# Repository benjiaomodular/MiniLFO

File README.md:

# MiniLFO

A super simple 2HP triangle wave LFO for Eurorack modular synth. This is roughly based on [David Haillant's Simple LFO](https://www.davidhaillant.com/wp/wp-content/uploads/lfo-1.5b-20210205.pdf).

More info on my website: https://benjiaomodular.com/posts/minilfo

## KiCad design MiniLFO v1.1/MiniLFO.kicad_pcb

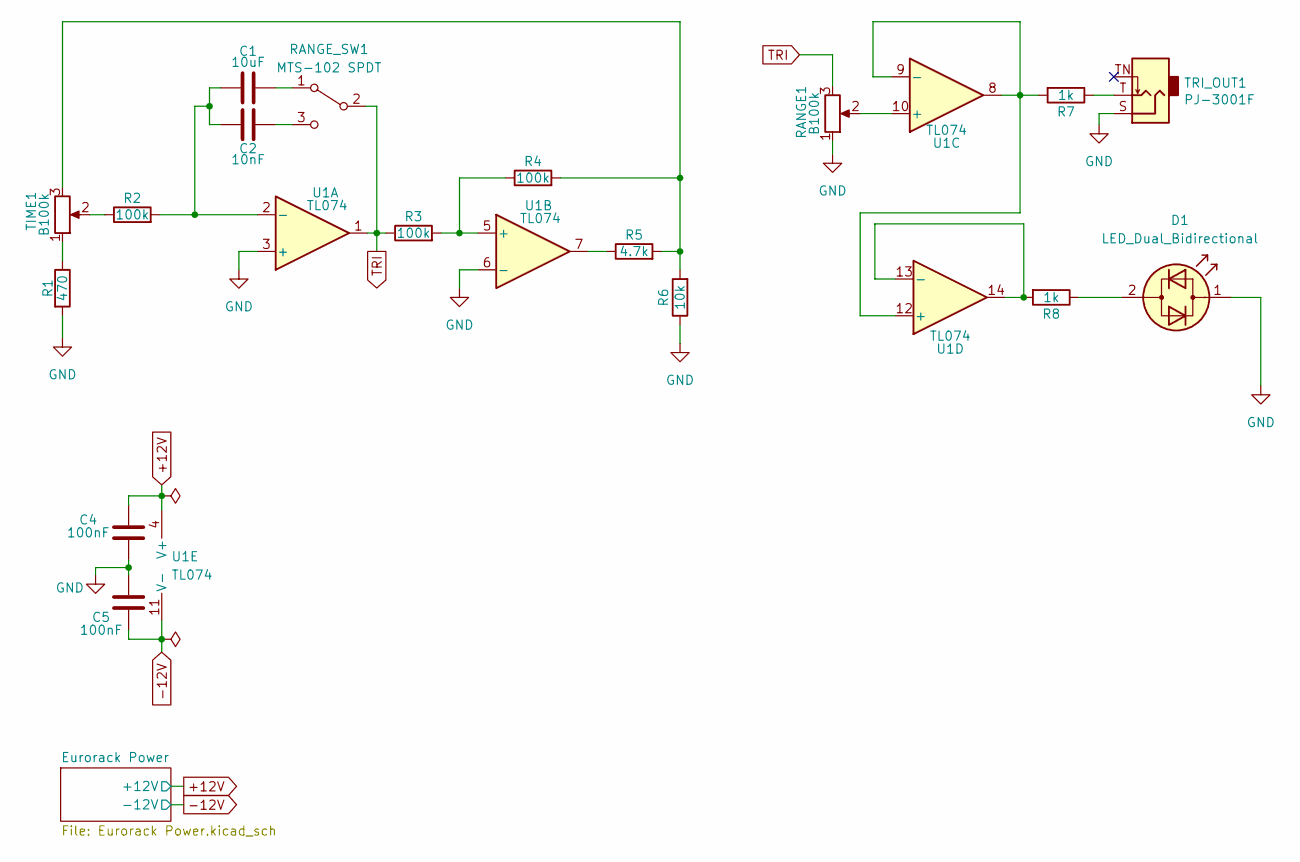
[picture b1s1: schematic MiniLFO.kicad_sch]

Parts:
C1: 10uF; Capacitor_Radial_D5.0mm_P2.5mm; Manufacturers Part Numb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 ECE-A1VN100UB
C2: 10nF; Capacitor_Rect_L7.2mm_W2.5mm_P5.00mm; Manufacturers Part Numb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 MMK5103K50J01L4BULK
C4, C5: 100nF; C_0603_1608Metric_Pad1.08x0.95mm_HandSolder; Manufacturers Part Numb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 R82EC3100DQ70K
D1: LED_Dual_Bidirectional; LED_D3.0mm; Manufacturers Part Numb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 3ARG4HWC
R1: 470; R_0603_1608Metric_Pad0.98x0.95mm_HandSolder; Manufacturers Part Numb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 RC0603FR-7W470RL
R2, R3, R4: 100k; R_0603_1608Metric_Pad0.98x0.95mm_HandSolder; Manufacturers Part Numb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 RC0603FR-07100KL
R5: 4.7k; R_0603_1608Metric_Pad0.98x0.95mm_HandSolder; Manufacturers Part Numb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 RC0603FR-074K7L
R6: 10k; R_0603_1608Metric_Pad0.98x0.95mm_HandSolder; Manufacturers Part Numb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 AC0603FR-0710KL
R7, R8: 1k; R_0603_1608Metric_Pad0.98x0.95mm_HandSolder; Manufacturers Part Numb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 RC0603FR-071KL
RANGE1: B100k; Potentiometer_RV09; Manufacturers Part Numb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 RV09AF-40-20K-B100K
RANGE_SW1: MTS-102 SPDT; ToggleSwitch_MTS-102_SPDT; Manufacturers Part Numb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 Mini Toggle Switch SPDT On-On
TIME1: B100k; Potentiometer_RV09; Manufacturers Part Numb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 RV09AF-40-20K-B100K
TRI_OUT1: PJ-3001F; AudioJack_3.5mm; Manufacturers Part Numb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 PJ-3001F
U1: TL074; SOIC-14_3.9x8.7mm_P1.27mm; Manufacturers Part Numb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 TL074ACDT

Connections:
+12V: C4.2, U1.4 (V+); also elsewhere on the board
-12V: C5.1, U1.11 (V-); also elsewhere on the board
GND: C4.1, C5.2, D1.1 (KA), R1.2, R6.1, RANGE1.1, TRI_OUT1.S, U1.3 (+), U1.6 (-); also elsewhere on the board
unnamed: C1.1, C2.1, R2.2, U1.2 (-)
unnamed: C1.2, RANGE_SW1.1 (A)
unnamed: C2.2, RANGE_SW1.3 (C)
unnamed: D1.2 (AK), R8.1
unnamed: R1.1, TIME1.1
unnamed: R2.1, TIME1.2
unnamed: R3.2, R4.1, U1.5 (+)
unnamed: R4.2, R5.2, R6.2, TIME1.3
unnamed: R5.1, U1.7
unnamed: R7.1, TRI_OUT1.T
unnamed: R7.2, U1.8, U1.9 (-), U1.12 (+)
unnamed: R8.2, U1.13 (-), U1.14
unnamed: RANGE1.2, U1.10 (+)
TRI: R3.1, RANGE1.3, RANGE_SW1.2 (B), U1.1

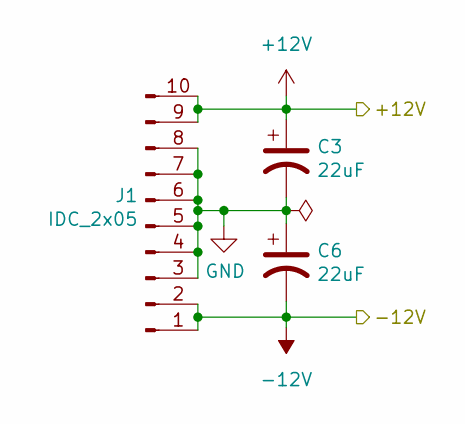
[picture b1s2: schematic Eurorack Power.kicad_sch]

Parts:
C3, C6: 22uF; C_0805_2012Metric_Pad1.18x1.45mm_HandSolder; Mfg # CC0805KRX7R9BB104; LCSC Part # C49678
J1: IDC_2x05; IDC-Header_2x05_P2.54mm_Vertical; Manufacturers Part Numb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 X9555WV-2X05-6TV01; LCSC Part # C706914

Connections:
+12V: C3.1, J1.9, J1.10; also elsewhere on the board
-12V: C6.2, J1.1, J1.2; also elsewhere on the board
GND: C3.2, C6.1, J1.3, J1.4, J1.5, J1.6, J1.7, J1.8; also elsewhere on the board

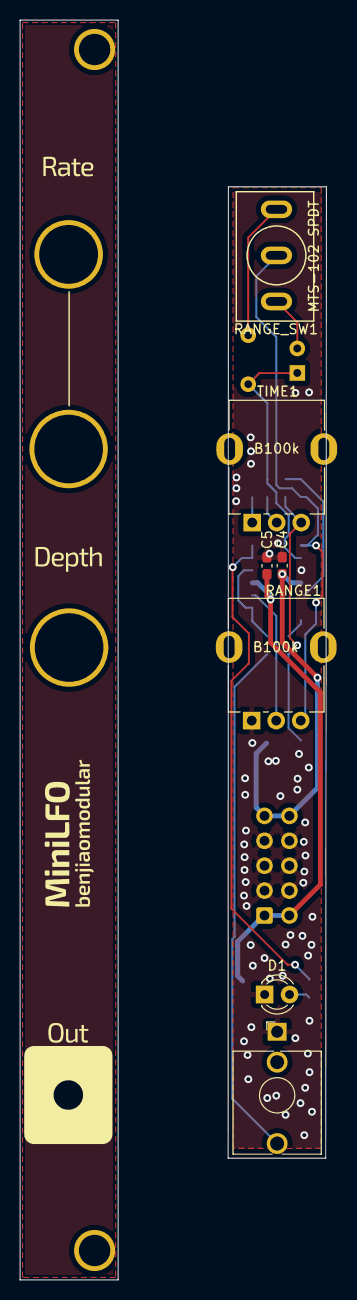
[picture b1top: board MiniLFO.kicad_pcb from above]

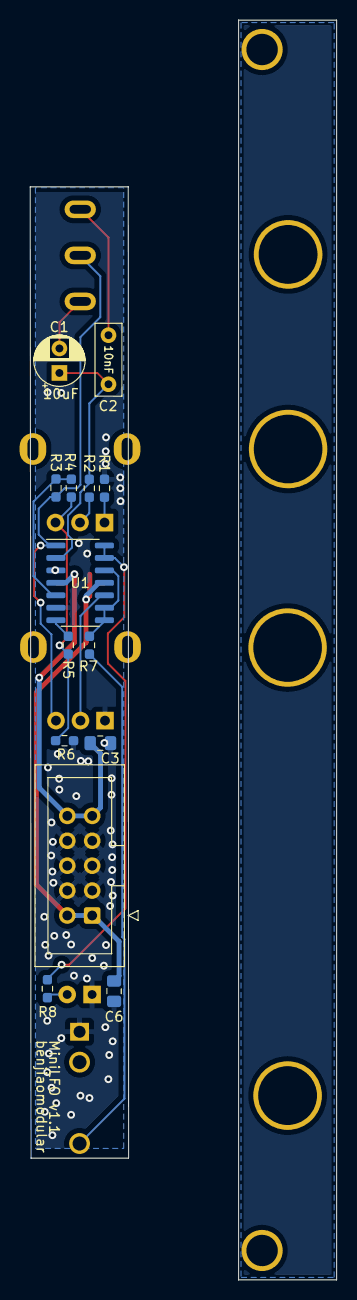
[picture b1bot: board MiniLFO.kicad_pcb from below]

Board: 2 copper layers, 10.0 x 99.1 mm, 21 parts (14 on the bottom side), 17 nets.

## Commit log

2023-02-18 hello git
2023-02-18 Cleanup old files
2023-04-19 Updated docs
2023-04-19 Show schematic
2023-04-19 Fixed images
2023-04-19 Added complete bom
2023-04-19 Renamed BOM
2023-04-19 Updated BOM with parts numbers
2023-04-19 Added license
2023-04-20 cleanup
